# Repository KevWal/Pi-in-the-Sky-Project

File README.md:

# Pi-in-the-Sky-Project

Random stuff associated with PITS project

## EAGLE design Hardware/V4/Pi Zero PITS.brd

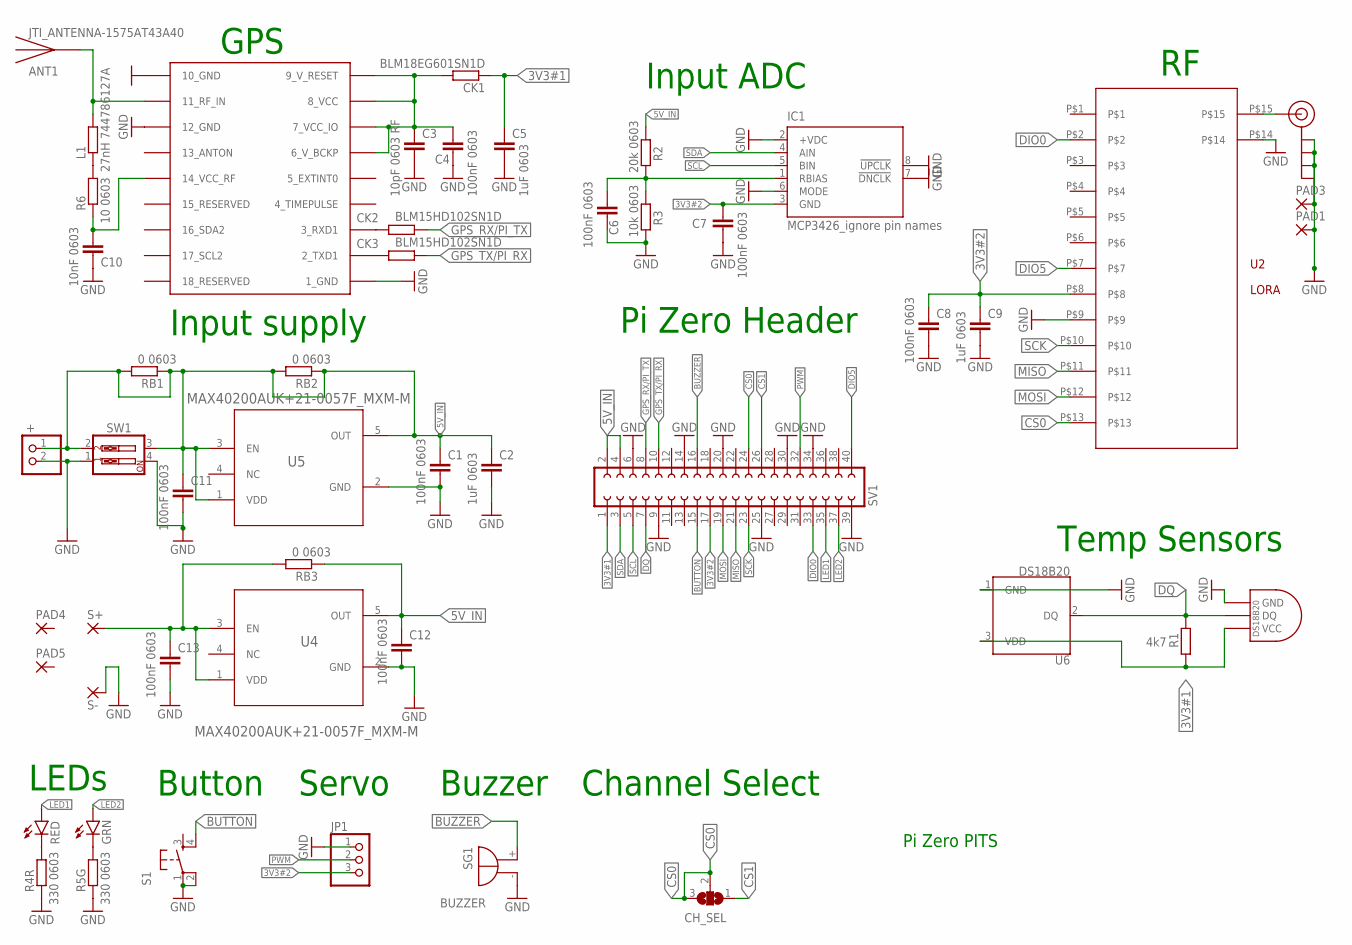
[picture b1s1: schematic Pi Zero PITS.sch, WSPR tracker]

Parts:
18B20Z: DS1820SOIC; DS18B20_SOIC
+: PINHD-1X2; 1X02
ANT1: JTI_ANTENNA-1575AT43A40
C1, C4, C6, C7, C8, C11, C12, C13: 100nF 0603; C0603K
C2, C5, C9: 1uF 0603; C0603K
C3: 10pF 0603 RF; C0603K
C10: 10nF 0603; C0603K
CH_SEL: SJ2W; SJ_2
CK1: BLM18EG601SN1D; R0603
CK2, CK3: BLM15HD102SN1D; R0402
GRN: LEDSML0603; SML0603
IC1: MCP3426_ignore pin names; SOIC08
J$2: SMA_EDGE; SMA-EDGE
JP1: PINHD-1X3; 1X03
L1: 27nH 744786127A; R0603
PAD1, PAD3: SMD5; SMD2,54-5,08
PAD4, PAD5: SMD2SMD_KW; SMD_SMALL
R1: 4k7; R0603
R2: 20k 0603; R0603
R3: 10k 0603; R0603
R4R, R5G: 330 0603; R0603
R6: 10 0603; R0603
RB1, RB2, RB3: 0 0603; R0603
RED: LEDSML0603; SML0603
S1: DTS-6
S+: SMD2SMD_KW; SMD_SMALL
S-: S-; SMD_SMALL
SG1: BUZZER; BMT1205XH7.5
SV1: FE20-2
SW1: SW_DIP-2; EDG-02
U1: U1; UBLOX_MAX-6
U2: LORA; LORA_DRF
U4, U5: MAX40200AUK+21-0057F_MXM-M; 21-0057F_MXM-M
U6: DS18B20; TO-92-TO92127P495H2044-3

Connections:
3V3#1: 18B20Z.VCC, C5.1, CK1.1, R1.1, SV1.1, U6.3 (VDD)
3V3#2: C7.1, C8.1, C9.1, IC1.3 (GND), JP1.3, SV1.17, U2.P$8
5V_IN: +.1, C1.1, C2.1, C11.1, C12.1, R2.1, RB1.1, RB1.2, RB2.1, RB2.2, RB3.1, SV1.2, SV1.4, SW1.2, SW1.3, U4.5 (OUT), U5.1 (VDD), U5.3 (EN), U5.5 (OUT)
BUTTON: S1.4, SV1.15
BUZZER: SG1.+, SV1.16
CS0: CH_SEL.2, CH_SEL.3, SV1.24, U2.P$13
CS1: CH_SEL.1, SV1.26
DIO0: SV1.33, U2.P$2
DIO5: SV1.40, U2.P$7
DQ: 18B20Z.DQ, R1.2, SV1.7, U6.2 (DQ)
GND: 18B20Z.GND, +.2, C1.2, C2.2, C3.2, C4.2, C5.2, C6.2, C7.2, C8.2, C9.2, C10.2, C11.2, C12.2, C13.2, IC1.2 (+VDC), IC1.6 (MODE), IC1.7 (!DNCLK), IC1.8 (!UPCLK), J$2.GND@0 (GND), J$2.GND@1 (GND), J$2.GND@2 (GND), J$2.GND@3 (GND), JP1.1, PAD1.1, PAD3.1, R3.2, R4R.1, R5G.1, S1.1, S1.2, S-.1, SG1.-, SV1.6, SV1.9, SV1.14, SV1.20, SV1.25, SV1.30, SV1.34, SV1.39, SW1.1, SW1.4, U1.1_GND, U1.10_GND, U1.12_GND, U2.P$9, U2.P$14, U4.2 (GND), U5.2 (GND), U6.1 (GND)
GPS_RX/PI_TX: CK2.2, SV1.8
GPS_TX/PI_RX: CK3.2, SV1.10
LED1: RED.A, SV1.35
LED2: GRN.A, SV1.37
MISO: SV1.21, U2.P$11
MOSI: SV1.19, U2.P$12
unnamed: J$2.SIG (SIGNAL), U2.P$15
unnamed: GRN.C, R5G.2
unnamed: CK2.1, U1.3_RXD1
unnamed: R4R.2, RED.C
unnamed: CK3.1, U1.2_TXD1
unnamed: C10.1, R6.1, U1.14_VCC_RF
unnamed: ANT1.FEED, L1.2, U1.11_RF_IN
unnamed: C6.1, IC1.1 (RBIAS), R2.2, R3.1
unnamed: L1.1, R6.2
unnamed: C3.1, C4.1, CK1.2, U1.6_V_BCKP, U1.7_VCC_IO, U1.8_VCC, U1.9_V_RESET
unnamed: C13.1, RB3.2, S+.1, U4.1 (VDD), U4.3 (EN)
PWM: JP1.2, SV1.32
SCK: SV1.23, U2.P$10
SCL: IC1.5 (BIN), SV1.5
SDA: IC1.4 (AIN), SV1.3

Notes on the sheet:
Temp Sensors
Servo
Buzzer
Button
GPS
Pi Zero Header
LEDs
Input supply
Input ADC
Channel Select
Pi Zero PITS

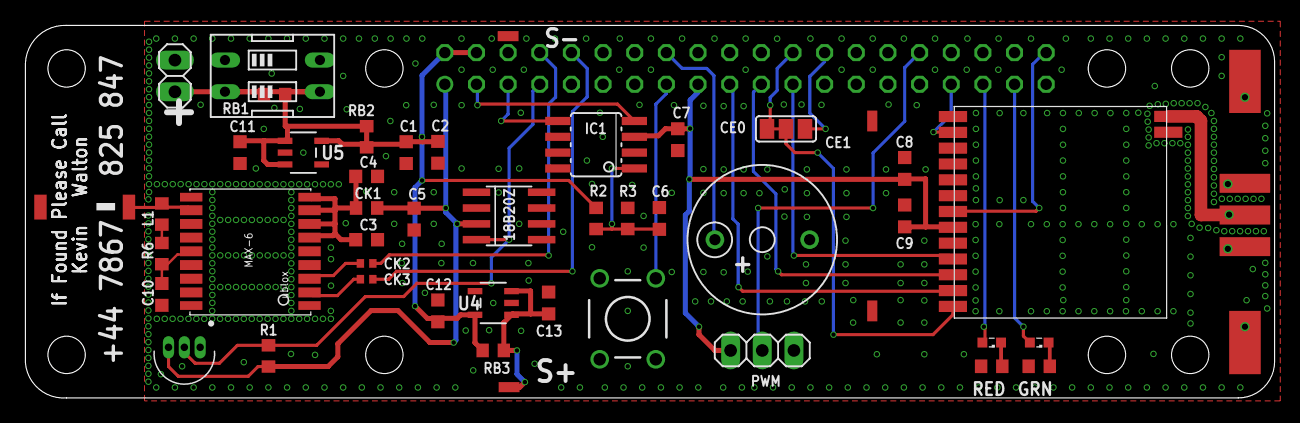
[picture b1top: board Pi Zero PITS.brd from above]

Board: 2 copper layers, 100.2 x 29.9 mm, 50 parts (1 on the bottom side), 32 nets.

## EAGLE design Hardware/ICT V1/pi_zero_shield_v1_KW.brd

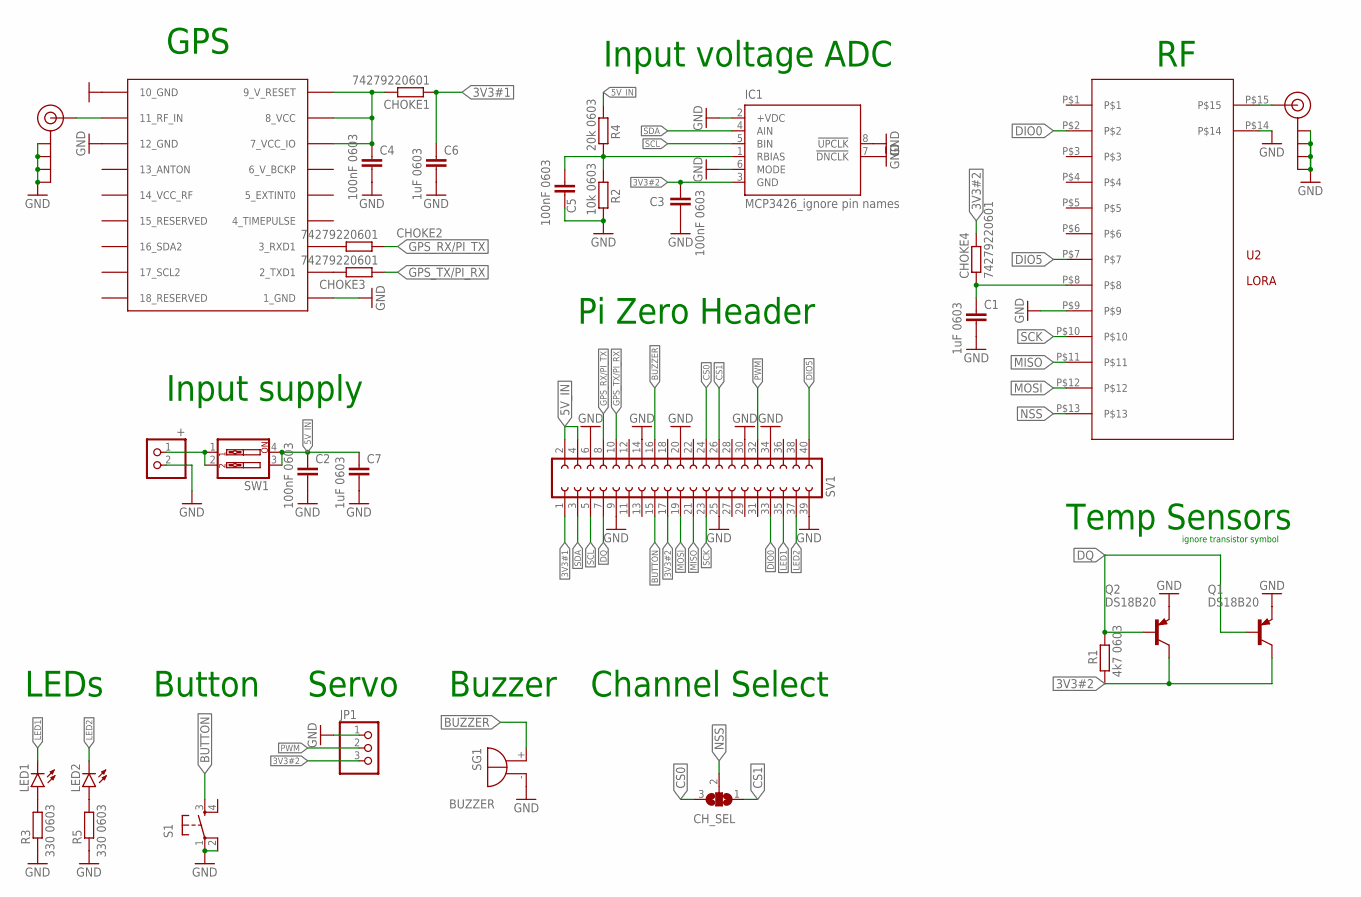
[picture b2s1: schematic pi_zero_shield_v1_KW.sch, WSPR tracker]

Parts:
+: PINHD-1X2; 1X02
C1, C6, C7: 1uF 0603; C0603K
C2, C3, C4, C5: 100nF 0603; C0603K
CHOKE1, CHOKE2, CHOKE3, CHOKE4: 74279220601; M0805
CH_SEL: SJ2W; SJ_2
IC1: MCP3426_ignore pin names; SOIC08
J$1, J$2: SMA_EDGE; SMA-EDGE
JP1: PINHD-1X3; 1X03
LED1, LED2: LEDSML0603; SML0603
Q1, Q2: DS18B20; TO92-CBE
R1: 4k7 0603; R0603
R2: 10k 0603; R0603
R3, R5: 330 0603; R0603
R4: 20k 0603; R0603
S1: DTS-6
SG1: BUZZER; BMT1205XH7.5
SV1: FE20-2
SW1: SW_DIP-2; EDG-02
U1: U1; UBLOX_MAX-6
U2: LORA; LORA_DRF

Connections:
3V3#1: C6.1, CHOKE1.1, SV1.1
3V3#2: C3.1, CHOKE4.2, IC1.3 (GND), JP1.3, Q1.C, Q2.C, R1.1, SV1.17
5V_IN: C2.1, C7.1, R4.1, SV1.2, SV1.4, SW1.3, SW1.4
BUTTON: S1.3, SV1.15
BUZZER: SG1.+, SV1.16
CS0: CH_SEL.3, SV1.24
CS1: CH_SEL.1, SV1.26
DIO0: SV1.33, U2.P$2
DIO5: SV1.40, U2.P$7
DQ: Q1.B, Q2.B, R1.2, SV1.7
DRF_VCC: C1.1, CHOKE4.1, U2.P$8
GND: +.2, C1.2, C2.2, C3.2, C4.2, C5.2, C6.2, C7.2, IC1.2 (+VDC), IC1.6 (MODE), IC1.7 (!DNCLK), IC1.8 (!UPCLK), J$1.GND@0 (GND), J$1.GND@1 (GND), J$1.GND@2 (GND), J$1.GND@3 (GND), J$2.GND@0 (GND), J$2.GND@1 (GND), J$2.GND@2 (GND), J$2.GND@3 (GND), JP1.1, Q1.E, Q2.E, R2.2, R3.1, R5.1, S1.1, S1.2, SG1.-, SV1.6, SV1.9, SV1.14, SV1.20, SV1.25, SV1.30, SV1.34, SV1.39, U1.1_GND, U1.10_GND, U1.12_GND, U2.P$9, U2.P$14
GPS_RX/PI_TX: CHOKE2.1, SV1.8
GPS_TX/PI_RX: CHOKE3.1, SV1.10
LED1: LED1.C, SV1.35
LED2: LED2.C, SV1.37
MISO: SV1.21, U2.P$11
MOSI: SV1.19, U2.P$12
unnamed: +.1, SW1.1, SW1.2
unnamed: J$2.SIG (SIGNAL), U2.P$15
unnamed: LED1.A, R3.2
unnamed: CHOKE2.2, U1.3_RXD1
unnamed: LED2.A, R5.2
unnamed: CHOKE3.2, U1.2_TXD1
unnamed: C4.1, CHOKE1.2, U1.7_VCC_IO, U1.8_VCC, U1.9_V_RESET
unnamed: J$1.SIG (SIGNAL), U1.11_RF_IN
unnamed: C5.1, IC1.1 (RBIAS), R2.1, R4.2
NSS: CH_SEL.2, U2.P$13
PWM: JP1.2, SV1.32
SCK: SV1.23, U2.P$10
SCL: IC1.5 (BIN), SV1.5
SDA: IC1.4 (AIN), SV1.3

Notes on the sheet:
Temp Sensors
Servo
Buzzer
Button
GPS
Pi Zero Header
LEDs
Input supply
Input voltage ADC
ignore transistor symbol
Channel Select

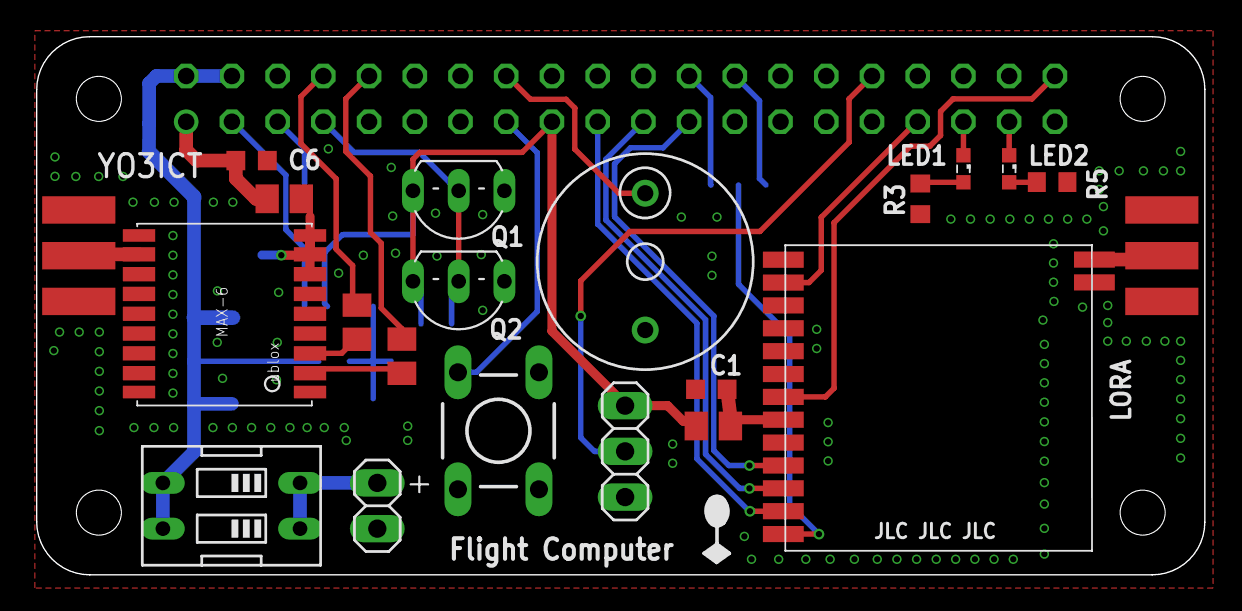
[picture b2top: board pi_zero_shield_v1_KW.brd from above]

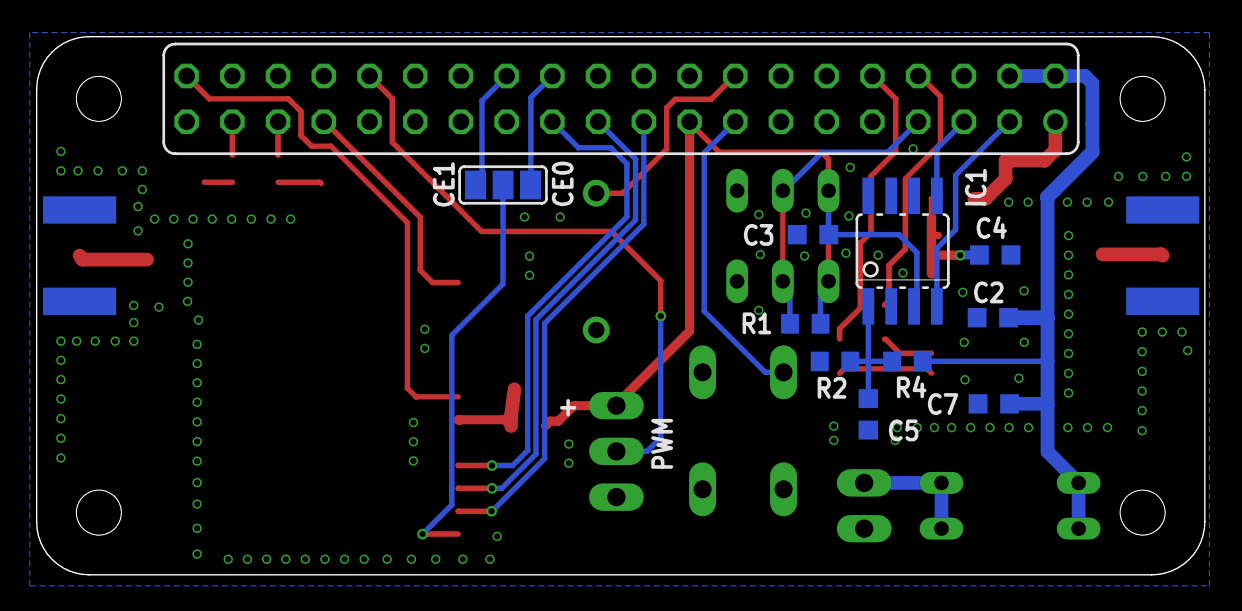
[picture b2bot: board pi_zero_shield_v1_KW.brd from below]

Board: 2 copper layers, 64.9 x 29.9 mm, 32 parts (11 on the bottom side), 32 nets.

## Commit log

2021-01-24 Start
2021-02-27 Flight 1 ad start own Hat
2021-03-02 Add Pics
2021-05-22 Printed
2022-08-04 Added NMEA Logs, minor PCB updates, Git notes and Pi Ethernet Driver
2022-08-06 Moved Solar support pads to between GPIO pins
2022-08-06 Restrict ground plane next to cut-able tracks
2022-09-15 Post Flight 2
2022-09-26 Updated IR2030 notes
2023-05-13 Typo
2023-05-16 Add Wedges
2023-05-31 Initial Upload
2024-03-10 Update GitNotes.txt
    Added link to nice instructions

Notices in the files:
parts and their libraries:
SparkFun-Sensors: Licensing: Creative Commons ShareAlike 4.0 International - https://creativecommons.org/licenses/by-sa/4.0
KEW_HF_V13: COPYRIGHT: Copyright (C) 2018 Accelerated Designs. All rights reserved
